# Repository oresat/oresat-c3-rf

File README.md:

# oresat-c3-rf
RF Sub systems for the C3 board.  This includes the transeiver ICs and all front-end components for the uplink and downlink radios.

## [AxSem_Profiles](AxSem_Profiles)
These are a bunch of profiles that initialize the AxSem RadioLab configuration program for testing and experiments.

## [KiCad](KiCad)
Evaluation board schematics and layouts in KiCad. Some of the older Eagle CAD boards are here converted to KiCAD.

## [block-diagrams](block-diagrams)
Block diagrams of the L band receiver and UHF transceiver hardware.

## [bom](bom)
Inventory and bill-of-materials (BOMs) for evaluation boards.

## [eagle](eagle)
Evaluation board schematics and layouts in EAGLE CAD.

## [link-models](link-models)
Complete link models for command/engineering channels, telemetry/public channels, and bulk mission data channels.

## [measurements](measurements)
Evaluation board measurements using lab tools.

## [simulations](simulations)
Evaluation board simulations using ADS and/or HFSS.

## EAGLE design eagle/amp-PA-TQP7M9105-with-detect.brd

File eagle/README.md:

## EAGLE CAD
Evaluation boards for the C3 board radios.

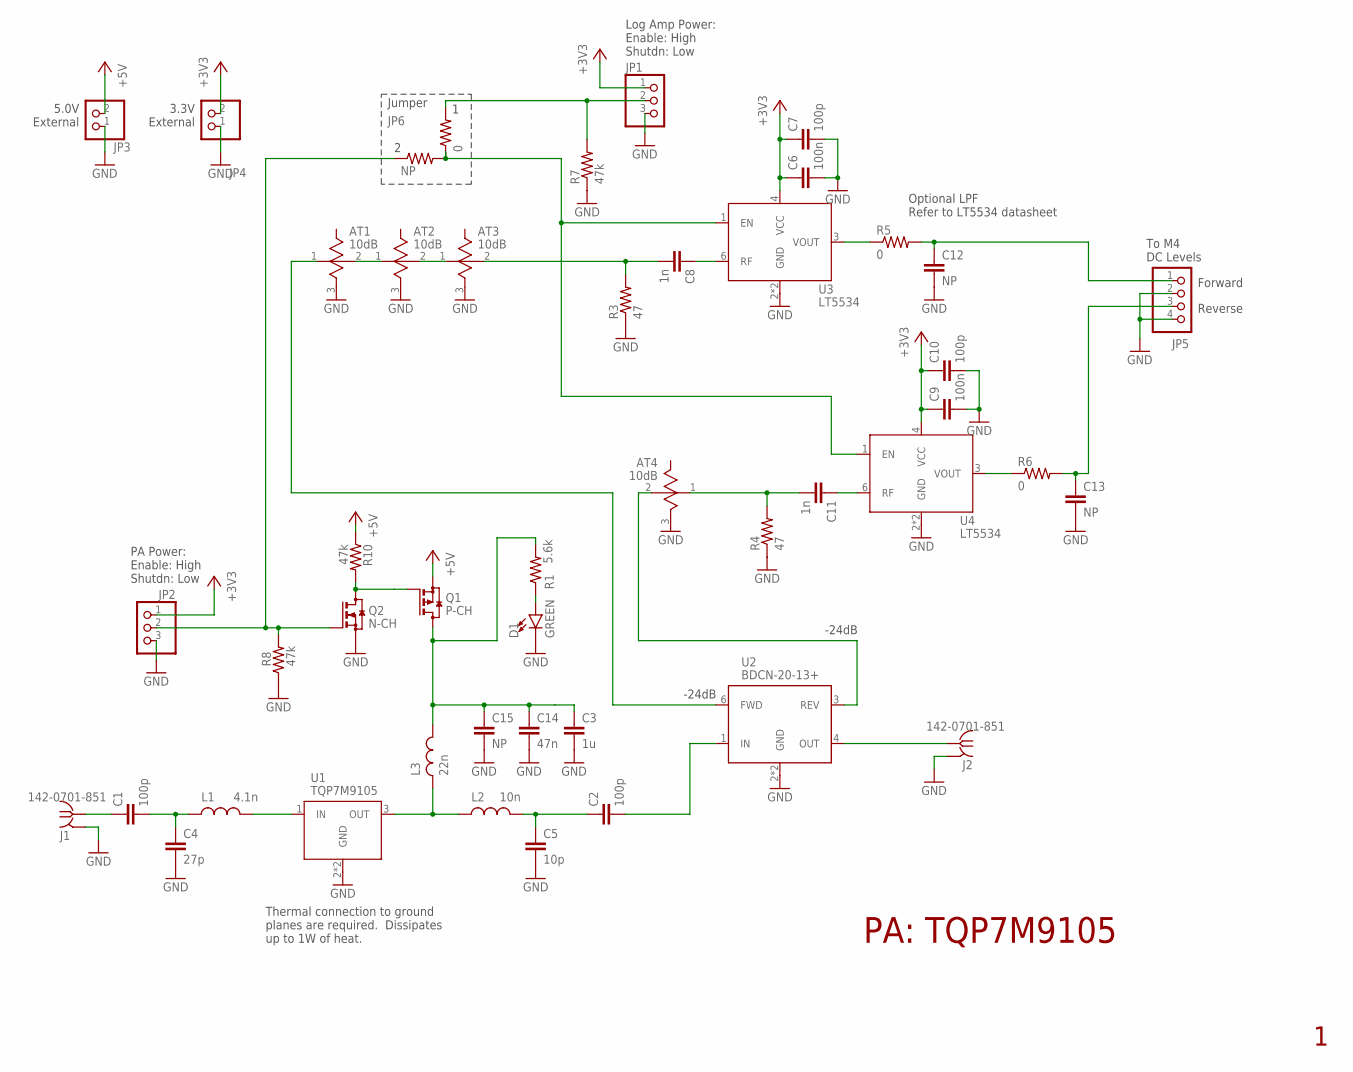
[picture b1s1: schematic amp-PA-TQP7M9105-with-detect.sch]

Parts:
AT1: 10dB; 0805
AT2, AT3, AT4: 10dB; 0603
C1: 100p; .0402-C-NOSILK
C2: 100p; .0603-C-NOSILK
C3: 1u; .0603-B-NOSILK
C4: 27p; .0402-C-NOSILK
C5: 10p; .0603-C-NOSILK
C6, C9: 100n; .0603-B-NOSILK
C7, C10: 100p; .0603-B-NOSILK
C8, C11: 1n; .0402-C-NOSILK
C12, C13, C15: NP; .0603-B-NOSILK
C14: 47n; .0603-B-NOSILK
D1: GREEN; LED-0603
J1, J2: 142-0701-851
JP1, JP2: PINHD-1X3; 1X03
JP3, JP4: PINHD-1X2; 1X02
JP5: PINHD-1X4; 1X04
JP6: NP; .0603-B-NOSILK
L1: 4.1n; .0402-C-NOSILK
L2: 10n; .0603-C-NOSILK@1
L3: 22n; .0805-C-NOSILK
Q1: P-CH; SOT23
Q2: N-CH; SOT23
R1: 5.6k; .0603-B-NOSILK
R3, R4: 47; .0402-C-NOSILK
R5, R6, R9: 0; .0603-B-NOSILK
R7, R8, R10: 47k; .0402-B-NOSILK
U1: TQP7M9105
U2: BDCN-20-13+
U3, U4: LT5534; SC70

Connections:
+3V3: C6.1, C7.1, C9.1, C10.1, JP1.1, JP2.1, JP4.2, U3.4 (VCC), U4.4 (VCC)
+5V: JP3.2, Q1.2 (S), R10.1
CAPS: C3.1, C14.1, C15.1, L3.2, Q1.3 (D), R1.2
FWD: C12.1, JP5.1, R5.2
GND: AT1.3 (GND), AT2.3 (GND), AT3.3 (GND), AT4.3 (GND), C3.2, C4.2, C5.2, C6.2, C7.2, C9.2, C10.2, C12.2, C13.2, C14.2, C15.2, D1.C, J1.GND1 (GND), J1.GND2 (GND), J1.GND3 (GND), J1.GND4 (GND), J2.GND1 (GND), J2.GND2 (GND), J2.GND3 (GND), J2.GND4 (GND), JP1.3, JP2.3, JP3.1, JP4.1, JP5.2, JP5.4, Q2.2 (S), R3.1, R4.1, R7.1, R8.1, U1.2 (GND), U1.PAD (GND), U2.2 (GND), U2.5 (GND), U3.2 (GND), U3.5 (GND), U4.2 (GND), U4.5 (GND)
unnamed: C1.1, J1.RF1 (RF)
unnamed: C2.2, U2.1 (IN)
unnamed: C1.2, C4.1, L1.1
unnamed: L1.2, U1.1 (IN)
unnamed: L2.1, L3.1, U1.3 (OUT)
unnamed: C2.1, C5.1, L2.2
unnamed: J2.RF1 (RF), U2.4 (OUT)
unnamed: C8.1, U3.6 (RF)
unnamed: AT3.2, C8.2, R3.2
unnamed: JP1.2, R7.2, R9.2
unnamed: C11.1, U4.6 (RF)
unnamed: AT4.1, C11.2, R4.2
unnamed: JP6.2, R9.1, U3.1 (EN), U4.1 (EN)
unnamed: AT1.1, U2.6 (FWD)
unnamed: AT1.2, AT2.1
unnamed: AT2.2, AT3.1
unnamed: R5.1, U3.3 (VOUT)
unnamed: R6.1, U4.3 (VOUT)
unnamed: AT4.2, U2.3 (REV)
unnamed: Q1.1 (G), Q2.3 (D), R10.2
unnamed: JP2.2, JP6.1, Q2.1 (G), R8.2
unnamed: D1.A, R1.1
REV: C13.1, JP5.3, R6.2

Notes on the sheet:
PA: TQP7M9105
Log Amp Power: Enable: High Shutdn: Low
To M4 DC Levels
Forward
Reverse
3.3V External
-24dB
PA Power: Enable: High Shutdn: Low
5.0V External
Optional LPF Refer to LT5534 datasheet
Thermal connection to ground planes are required. Dissipates up to 1W of heat.
Jumper

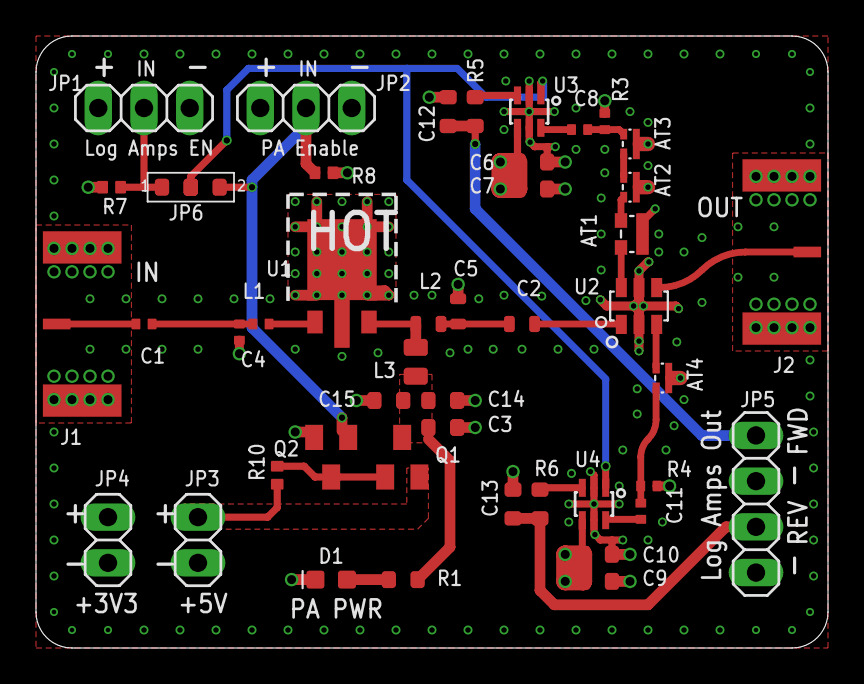
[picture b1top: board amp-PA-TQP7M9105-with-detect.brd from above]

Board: 4 copper layers, 44.0 x 34.0 mm, 46 parts (0 on the bottom side), 28 nets.

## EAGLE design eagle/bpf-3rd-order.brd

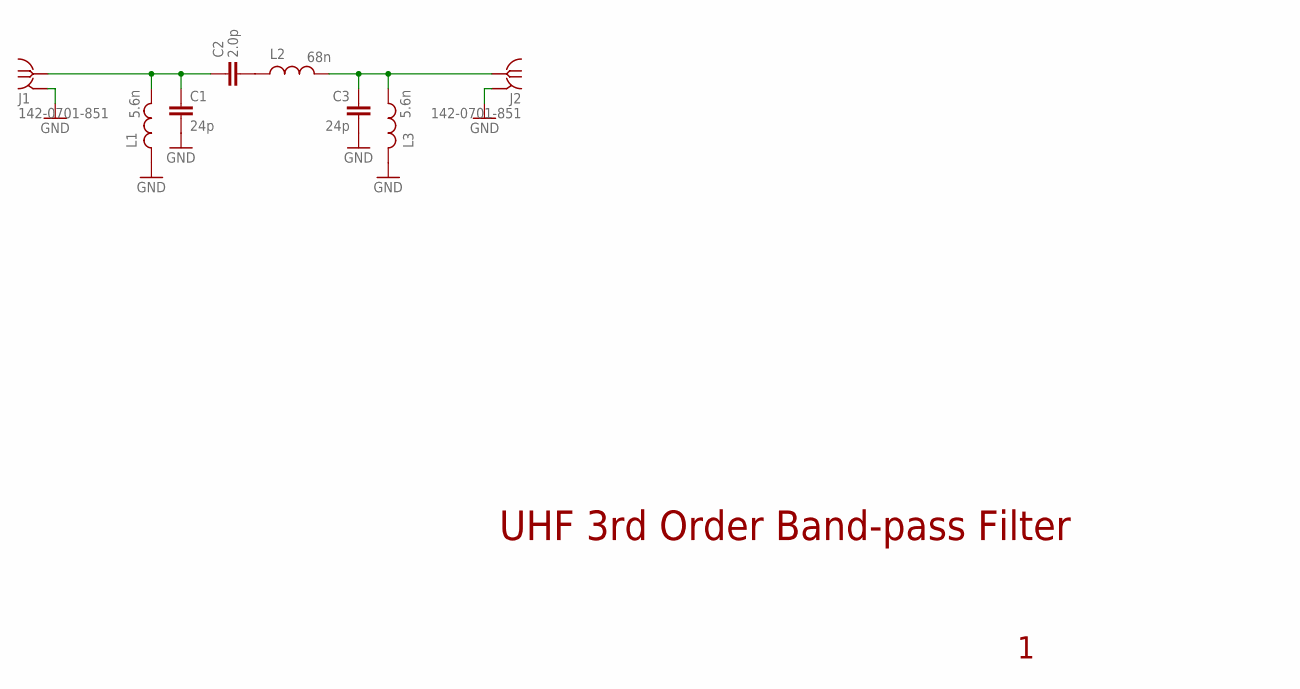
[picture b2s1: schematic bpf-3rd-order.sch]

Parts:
C1, C3: 24p; .0402-C-NOSILK
C2: 2.0p; .0402-C-NOSILK
J1, J2: 142-0701-851
L1, L3: 5.6n; .0402-C-NOSILK
L2: 68n; .0402-C-NOSILK

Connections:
GND: C1.2, C3.2, J1.GND1 (GND), J1.GND2 (GND), J1.GND3 (GND), J1.GND4 (GND), J2.GND1 (GND), J2.GND2 (GND), J2.GND3 (GND), J2.GND4 (GND), L1.1, L3.1
unnamed: C2.2, L2.1
unnamed: C1.1, C2.1, J1.RF1 (RF), L1.2
unnamed: C3.1, J2.RF1 (RF), L2.2, L3.2

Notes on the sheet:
UHF 3rd Order Band-pass Filter

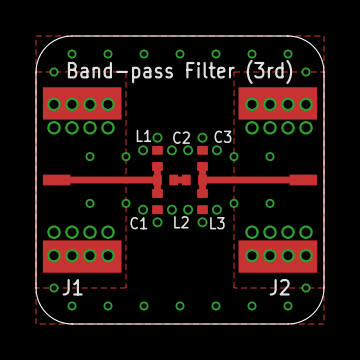
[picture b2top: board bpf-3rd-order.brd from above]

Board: 4 copper layers, 16.0 x 16.0 mm, 8 parts (0 on the bottom side), 4 nets.

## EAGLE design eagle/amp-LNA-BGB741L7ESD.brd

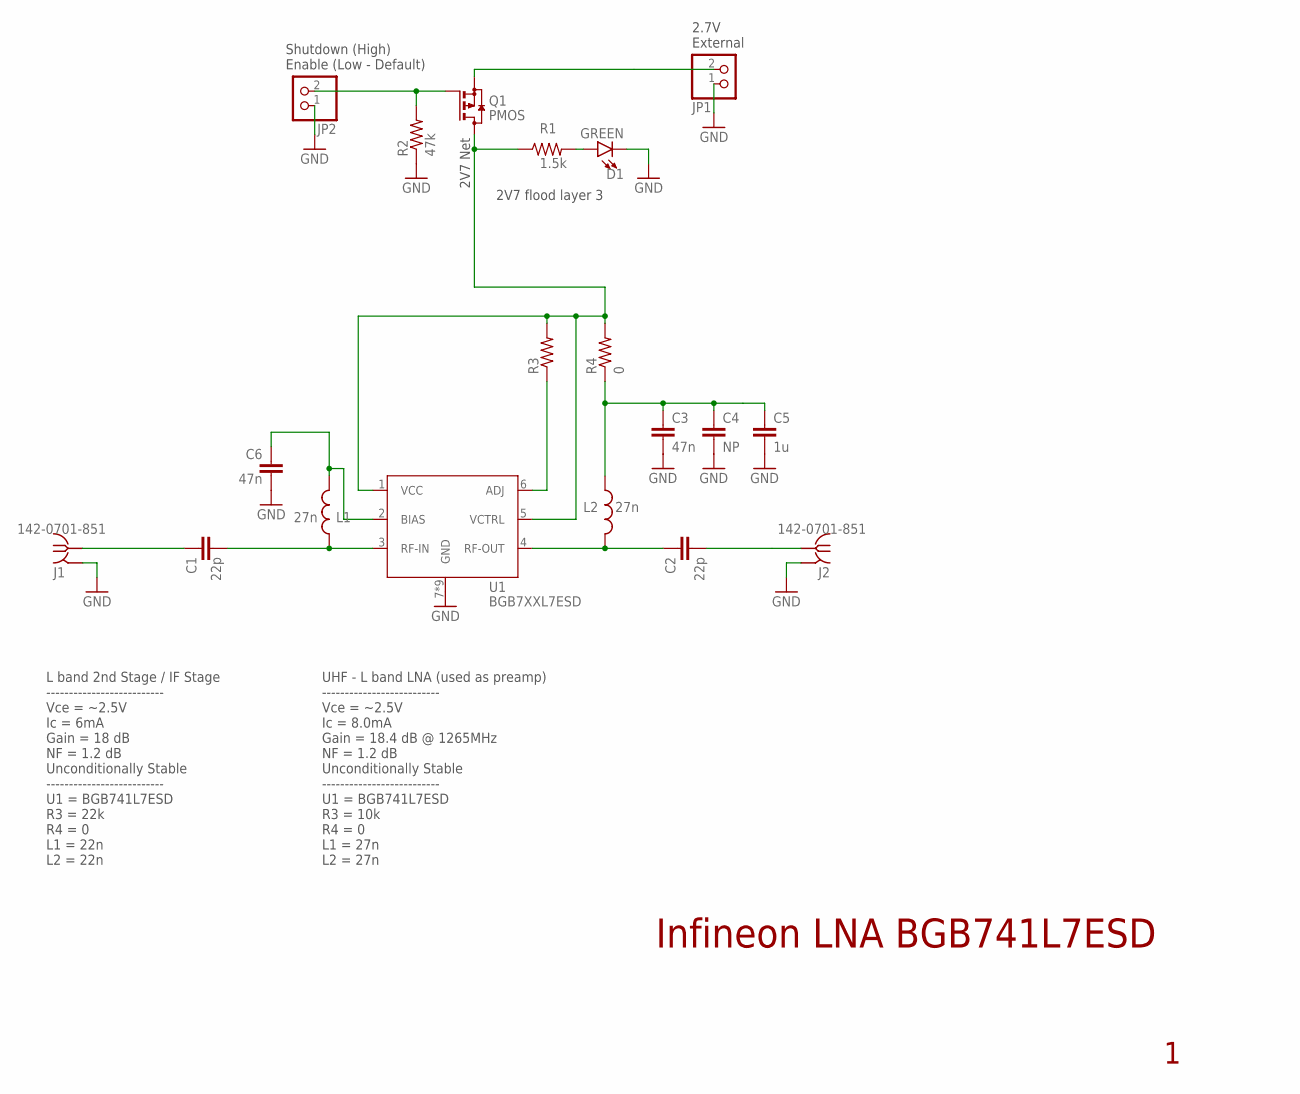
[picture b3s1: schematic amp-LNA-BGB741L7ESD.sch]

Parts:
C1, C2: 22p; .0402-C-NOSILK
C3, C6: 47n; .0603-B-NOSILK
C4: NP; .0603-B-NOSILK
C5: 1u; .0603-B-NOSILK
D1: GREEN; LED-0603
J1, J2: 142-0701-851
JP1, JP2: PINHD-1X2; 1X02
L1, L2: 27n; .0603-C-NOSILK
Q1: PMOS; SOT23
R1: 1.5k; .0603-B-NOSILK
R2: 47k; .0402-B-NOSILK
R3: 27k / NP; .0603-B-NOSILK
R4: 0; .0603-B-NOSILK
U1: BGB7XXL7ESD

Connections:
2V7: Q1.3 (D), R1.1, R3.2, R4.2, U1.1 (VCC), U1.5 (VCTRL)
GND: C3.2, C4.2, C5.2, C6.2, D1.C, J1.GND1 (GND), J1.GND2 (GND), J1.GND3 (GND), J1.GND4 (GND), J2.GND1 (GND), J2.GND2 (GND), J2.GND3 (GND), J2.GND4 (GND), JP1.1, JP2.1, R2.1, U1.7 (GND), U1.8 (GND), U1.9 (GND), U1.10 (GND), U1.11 (GND), U1.12 (GND), U1.13 (GND), U1.14 (GND), U1.15 (GND)
unnamed: JP2.2, Q1.1 (G), R2.2
unnamed: C3.1, C4.1, C5.1, L2.1, R4.1
unnamed: C2.1, L2.2, U1.4 (RF-OUT)
unnamed: R3.1, U1.6 (ADJ)
unnamed: C6.1, L1.2, U1.2 (BIAS)
unnamed: D1.A, R1.2
unnamed: C1.2, L1.1, U1.3 (RF-IN)
RF-IN: C1.1, J1.RF1 (RF)
RF_OUT: C2.2, J2.RF1 (RF)
VEXT: JP1.2, Q1.2 (S)

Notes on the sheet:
Infineon LNA BGB741L7ESD
2.7V External
Shutdown (High) Enable (Low - Default)
2V7 flood layer 3
2V7 Net
L band 2nd Stage / IF Stage -------------------------- Vce = ~2.5V Ic = 6mA Gain = 18 dB NF = 1.2 dB Unconditionally Stable -------------------------- U1 = BGB741L7ESD R3 = 22k R4 = 0 L1 = 22n L2 = 22n
UHF - L band LNA (used as preamp) -------------------------- Vce = ~2.5V Ic = 8.0mA Gain = 18.4 dB @ 1265MHz NF = 1.2 dB Unconditionally Stable -------------------------- U1 = BGB741L7ESD R3 = 10k R4 = 0 L1 = 27n L2 = 27n

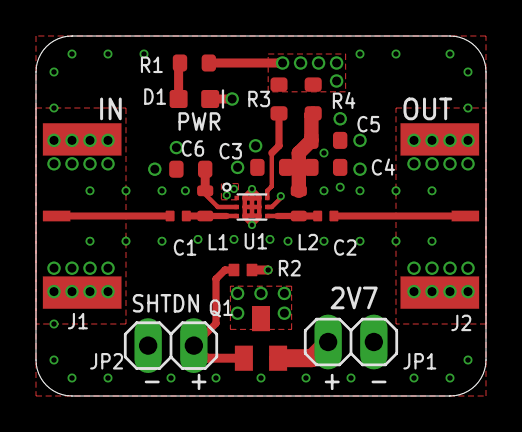
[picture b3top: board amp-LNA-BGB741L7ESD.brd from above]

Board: 4 copper layers, 25.0 x 20.0 mm, 19 parts (0 on the bottom side), 12 nets.

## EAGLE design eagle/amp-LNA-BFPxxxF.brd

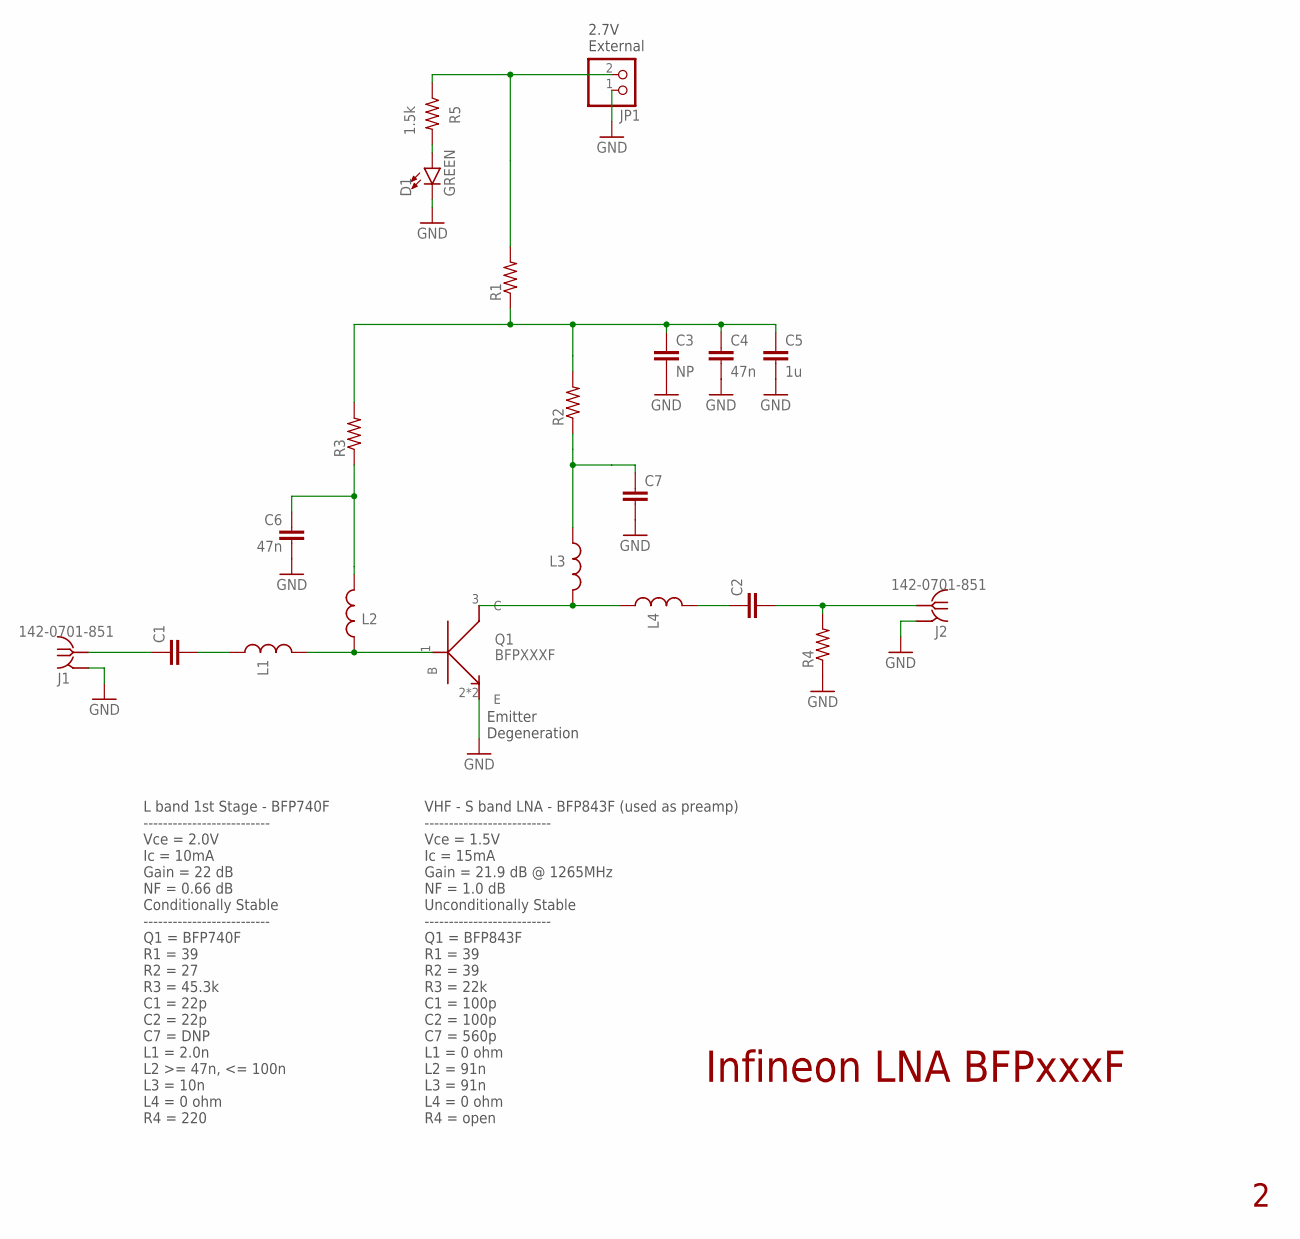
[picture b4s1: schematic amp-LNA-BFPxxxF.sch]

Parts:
C1, C2: C-EU0402-C-NOSILK; .0402-C-NOSILK
C3: NP; .0603-C-NOSILK
C4, C6: 47n; .0603-C-NOSILK
C5: 1u; .0603-C-NOSILK
C7: C-EU0402-B-NOSILK; .0402-B-NOSILK
D1: GREEN; LED-0603
J1, J2: 142-0701-851
JP1: PINHD-1X2; 1X02
L1, L4: L-US0402-C-NOSILK; .0402-C-NOSILK
L2, L3: L-US0603-C-NOSILK; .0603-C-NOSILK
Q1: BFPXXXF; TSFP4
R1, R2, R3, R4: R-US_0603-C-NOSILK; .0603-C-NOSILK
R5: 1.5k; .0603-C-NOSILK

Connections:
2V7: JP1.2, R1.2, R5.1
B: L1.2, L2.1, Q1.1 (B)
C: L3.2, L4.1, Q1.3 (C)
CAPS: C3.1, C4.1, C5.1, R1.1, R2.2, R3.2
GND: C3.2, C4.2, C5.2, C6.2, C7.2, D1.C, J1.GND1 (GND), J1.GND2 (GND), J1.GND3 (GND), J1.GND4 (GND), J2.GND1 (GND), J2.GND2 (GND), J2.GND3 (GND), J2.GND4 (GND), JP1.1, Q1.2 (E), Q1.4 (E), R4.1
unnamed: C2.1, L4.2
unnamed: C1.2, L1.1
unnamed: C7.1, L3.1, R2.1
unnamed: C6.1, L2.2, R3.1
unnamed: D1.A, R5.2
RF_IN: C1.1, J1.RF1 (RF)
RF_OUT: C2.2, J2.RF1 (RF), R4.2

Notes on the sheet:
Infineon LNA BFPxxxF
2.7V External
L band 1st Stage - BFP740F -------------------------- Vce = 2.0V Ic = 10mA Gain = 22 dB NF = 0.66 dB Conditionally Stable -------------------------- Q1 = BFP740F R1 = 39 R2 = 27 R3 = 45.3k C1 = 22p C2 = 22p C7 = DNP L1 = 2.0n L2 >= 47n, <= 100n L3 = 10n L4 = 0 ohm R4 = 220
Emitter Degeneration
VHF - S band LNA - BFP843F (used as preamp) -------------------------- Vce = 1.5V Ic = 15mA Gain = 21.9 dB @ 1265MHz NF = 1.0 dB Unconditionally Stable -------------------------- Q1 = BFP843F R1 = 39 R2 = 39 R3 = 22k C1 = 100p C2 = 100p C7 = 560p L1 = 0 ohm L2 = 91n L3 = 91n L4 = 0 ohm R4 = open

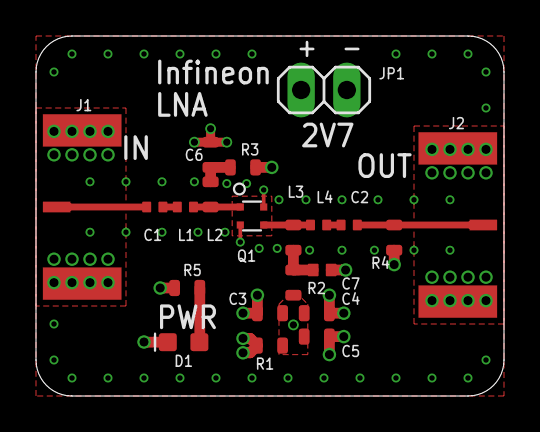
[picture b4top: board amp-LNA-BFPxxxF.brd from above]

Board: 4 copper layers, 26.0 x 20.0 mm, 21 parts (0 on the bottom side), 12 nets.

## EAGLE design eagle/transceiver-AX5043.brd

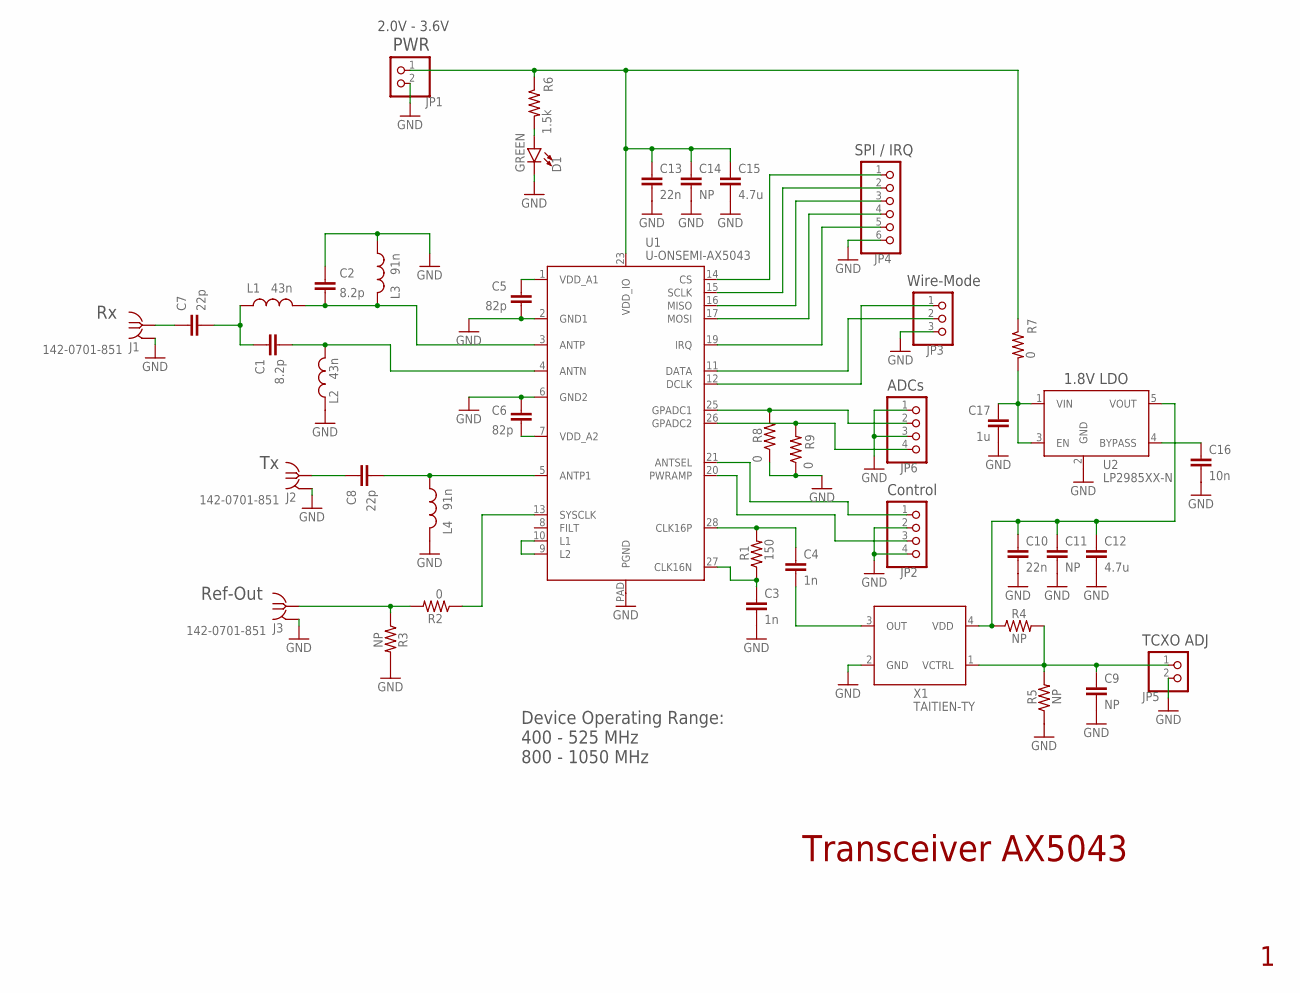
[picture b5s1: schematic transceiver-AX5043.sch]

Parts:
C1, C2: 8.2p; .0402-C-NOSILK
C3, C4: 1n; .0402-C-NOSILK
C5, C6: 82p; .0402-C-NOSILK
C7, C8: 22p; .0402-C-NOSILK
C9, C11, C14: NP; .0603-C-NOSILK
C10, C13: 22n; .0603-C-NOSILK
C12, C15: 4.7u; .0603-C-NOSILK
C16: 10n; .0603-C-NOSILK
C17: 1u; .0603-C-NOSILK
D1: GREEN; LED-0603
J1, J2, J3: 142-0701-851
JP1, JP5: PINHD-1X2; 1X02
JP2, JP6: PINHD-1X4; 1X04
JP3: PINHD-1X3; 1X03
JP4: PINHD-1X6; 1X06
L1, L2: 43n; .0402-C-NOSILK
L3, L4: 91n; .0603-C-NOSILK
R1: 150; .0402-C-NOSILK
R2, R8, R9: 0; .0402-C-NOSILK
R3: NP; .0402-C-NOSILK
R4, R5: NP; .0603-B-NOSILK
R6: 1.5k; .0603-B-NOSILK
R7: 0; .0603-C-NOSILK
U1: U-ONSEMI-AX5043; QFN28-5X5-WITH-CENTER-PAD
U2: LP2985XX-N; SOT-23
X1: TAITIEN-TY; 2.5X2.0

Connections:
1V8: C10.1, C11.1, C12.1, R4.1, U2.5 (VOUT), X1.4 (VDD)
2V7: C13.1, C14.1, C15.1, JP1.1, R6.1, R7.1, U1.23 (VDD_IO)
ADC1: JP6.2, R8.2, U1.25 (GPADC1)
ADC2: JP6.4, R9.2, U1.26 (GPADC2)
ANTN: C1.2, L2.2, U1.4 (ANTN)
ANTP: C2.2, L1.2, L3.1, U1.3 (ANTP)
ANTP1: C8.2, L4.2, U1.5 (ANTP1)
ANTSEL: JP2.1, U1.21 (ANTSEL)
CLKN: C3.1, R1.1, U1.27 (CLK16N)
CLKP: C4.1, R1.2, U1.28 (CLK16P)
CS: JP4.1, U1.14 (CS)
DATA: JP3.2, U1.11 (DATA)
DCLK: JP3.1, U1.12 (DCLK)
GND: C2.1, C3.2, C5.2, C6.1, C9.2, C10.2, C11.2, C12.2, C13.2, C14.2, C15.2, C16.2, C17.2, D1.C, J1.GND1 (GND), J1.GND2 (GND), J1.GND3 (GND), J1.GND4 (GND), J2.GND1 (GND), J2.GND2 (GND), J2.GND3 (GND), J2.GND4 (GND), J3.GND1 (GND), J3.GND2 (GND), J3.GND3 (GND), J3.GND4 (GND), JP1.2, JP2.2, JP2.4, JP3.3, JP4.6, JP5.2, JP6.1, JP6.3, L2.1, L3.2, L4.1, R3.2, R5.1, R8.1, R9.1, U1.2 (GND1), U1.6 (GND2), U1.PAD (PGND), U2.2 (GND), X1.2 (GND)
IRQ: JP4.5, U1.19 (IRQ)
MISO: JP4.3, U1.16 (MISO)
MOSI: JP4.4, U1.17 (MOSI)
unnamed: C5.1, U1.1 (VDD_A1)
unnamed: C17.1, R7.2, U2.1 (VIN), U2.3 (EN)
unnamed: U1.9 (L2), U1.10 (L1)
unnamed: C4.2, X1.3 (OUT)
unnamed: C1.1, C7.2, L1.1
unnamed: C9.1, JP5.1, R4.2, R5.2, X1.1 (VCTRL)
unnamed: D1.A, R6.2
unnamed: C16.1, U2.4 (BYPASS)
unnamed: C6.2, U1.7 (VDD_A2)
PWRAMP: JP2.3, U1.20 (PWRAMP)
REF-OUT: J3.RF1 (RF), R2.2, R3.1
RX: C7.1, J1.RF1 (RF)
SCLK: JP4.2, U1.15 (SCLK)
SYSCLK: R2.1, U1.13 (SYSCLK)
TX: C8.1, J2.RF1 (RF)

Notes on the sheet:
Transceiver AX5043
Ref-Out
PWR
SPI / IRQ
Wire-Mode
Control
TCXO ADJ
1.8V LDO
ADCs
Device Operating Range: 400 - 525 MHz 800 - 1050 MHz
2.0V - 3.6V

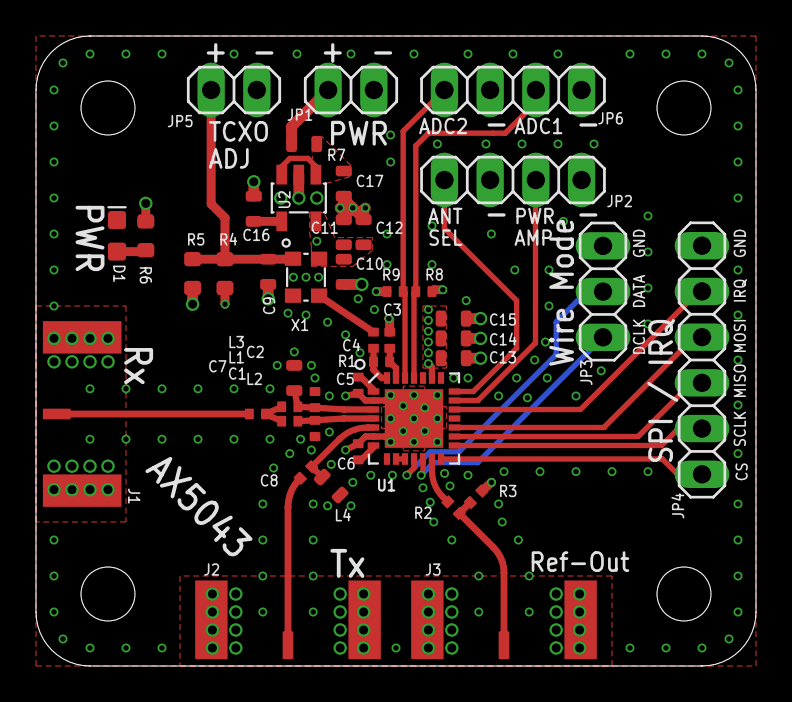
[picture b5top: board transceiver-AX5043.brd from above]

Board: 4 copper layers, 40.0 x 35.0 mm, 43 parts (0 on the bottom side), 32 nets.

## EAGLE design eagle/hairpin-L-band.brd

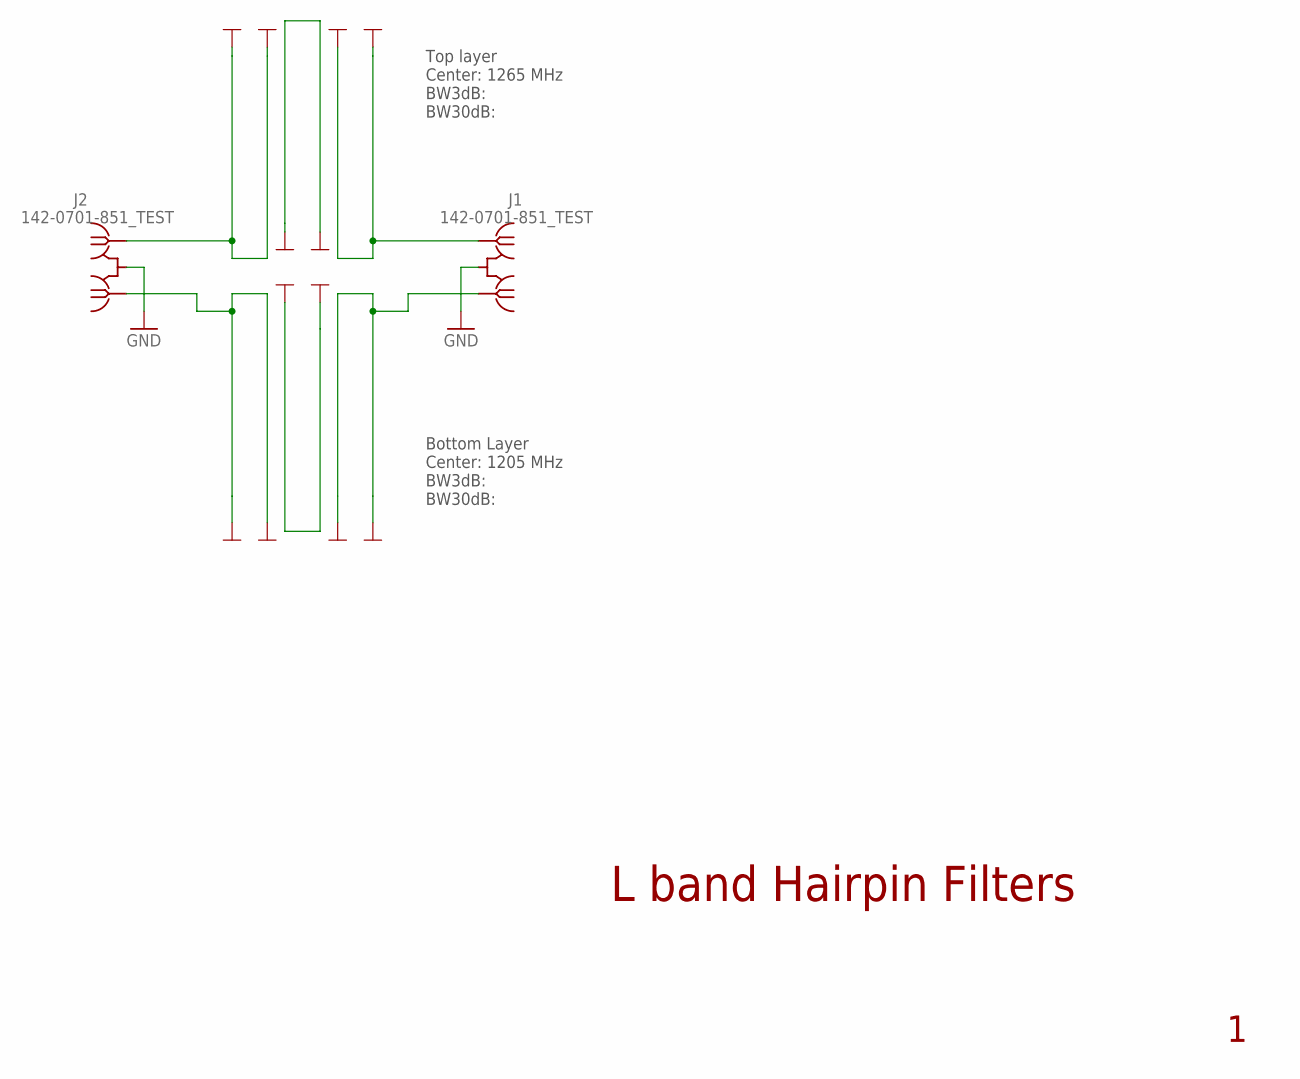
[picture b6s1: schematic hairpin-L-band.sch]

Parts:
J1, J2: 142-0701-851_TEST
U$1, U$2, U$3, U$4, U$5, U$6: PAD_0.6; 0.6MM
U$7, U$8, U$9, U$10, U$11, U$12: PAD_0.6_B; 0.6MM_B

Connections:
BLEFT: J2.RF2, U$11.END, U$12.END
BMID: U$9.END, U$10.END
BRIGHT: J1.RF2, U$7.END, U$8.END
GND: J1.GND1 (GND), J1.GND2 (GND), J1.GND3 (GND), J1.GND4 (GND), J2.GND1 (GND), J2.GND2 (GND), J2.GND3 (GND), J2.GND4 (GND)
TLEFT: J2.RF1, U$5.END, U$6.END
TMID: U$3.END, U$4.END
TRIGHT: J1.RF1, U$1.END, U$2.END

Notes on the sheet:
L band Hairpin Filters
Top layer Center: 1265 MHz BW3dB: BW30dB:
Bottom Layer Center: 1205 MHz BW3dB: BW30dB:

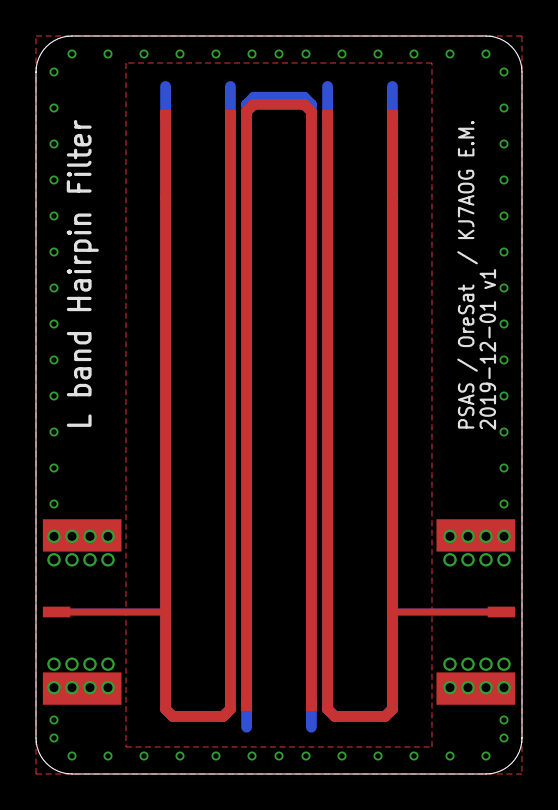
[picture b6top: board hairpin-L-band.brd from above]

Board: 4 copper layers, 27.0 x 41.0 mm, 14 parts (0 on the bottom side), 7 nets.

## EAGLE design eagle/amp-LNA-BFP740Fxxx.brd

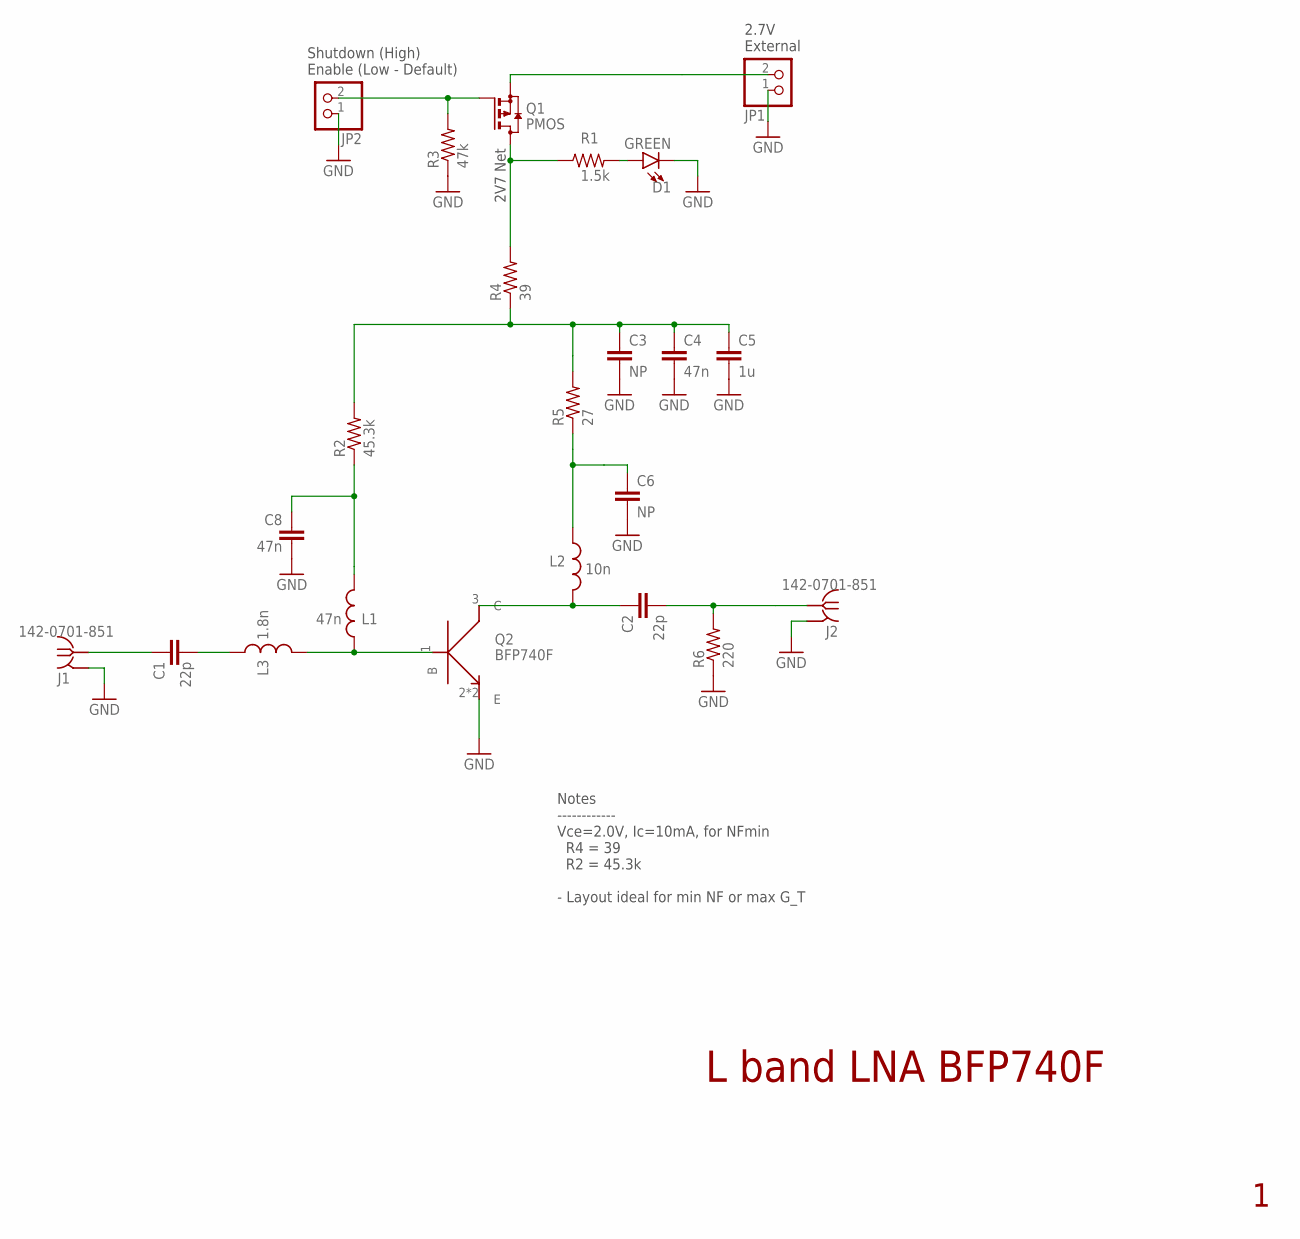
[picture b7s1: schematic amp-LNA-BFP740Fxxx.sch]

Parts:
C1, C2: 22p; .0402-C-NOSILK
C3: NP; .0603-C-NOSILK
C4, C8: 47n; .0603-C-NOSILK
C5: 1u; .0603-C-NOSILK
C6: NP; .0402-B-NOSILK
D1: GREEN; LED-0603
J1, J2: 142-0701-851
JP1, JP2: PINHD-1X2; 1X02
L1: 47n; .0603-C-NOSILK
L2: 10n; .0603-C-NOSILK
L3: 1.8n; .0402-C-NOSILK
Q1: PMOS; SOT23
Q2: BFP740F; TSFP4
R1: 1.5k; .0603-C-NOSILK
R2: 45.3k; .0603-C-NOSILK
R3: 47k; .0402-B-NOSILK
R4: 39; .0603-C-NOSILK
R5: 27; .0603-C-NOSILK
R6: 220; .0603-C-NOSILK

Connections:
2V7: Q1.3 (D), R1.1, R4.2
B: L1.1, L3.2, Q2.1 (B)
C: C2.1, L2.2, Q2.3 (C)
CAPS: C3.1, C4.1, C5.1, R2.2, R4.1, R5.2
GND: C3.2, C4.2, C5.2, C6.2, C8.2, D1.C, J1.GND1 (GND), J1.GND2 (GND), J1.GND3 (GND), J1.GND4 (GND), J2.GND1 (GND), J2.GND2 (GND), J2.GND3 (GND), J2.GND4 (GND), JP1.1, JP2.1, Q2.2 (E), Q2.4 (E), R3.1, R6.1
unnamed: JP2.2, Q1.1 (G), R3.2
unnamed: C1.2, L3.1
unnamed: C6.1, L2.1, R5.1
unnamed: C8.1, L1.2, R2.1
unnamed: D1.A, R1.2
RF_IN: C1.1, J1.RF1 (RF)
RF_OUT: C2.2, J2.RF1 (RF), R6.2
VEXT: JP1.2, Q1.2 (S)

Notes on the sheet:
L band LNA BFP740F
2.7V External
Shutdown (High) Enable (Low - Default)
2V7 Net
Notes ------------ Vce=2.0V, Ic=10mA, for NFmin R4 = 39 R2 = 45.3k - Layout ideal for min NF or max G_T

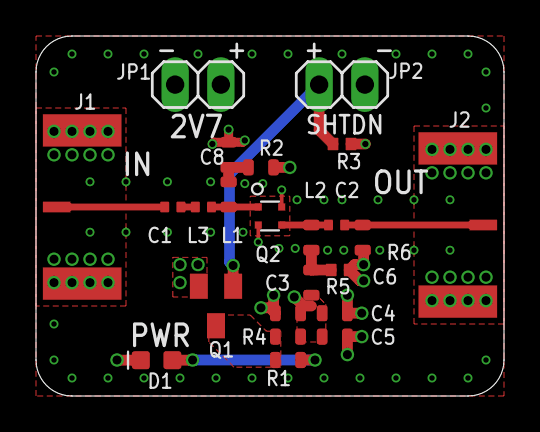
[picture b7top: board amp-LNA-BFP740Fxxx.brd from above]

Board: 4 copper layers, 26.0 x 20.0 mm, 23 parts (0 on the bottom side), 13 nets.

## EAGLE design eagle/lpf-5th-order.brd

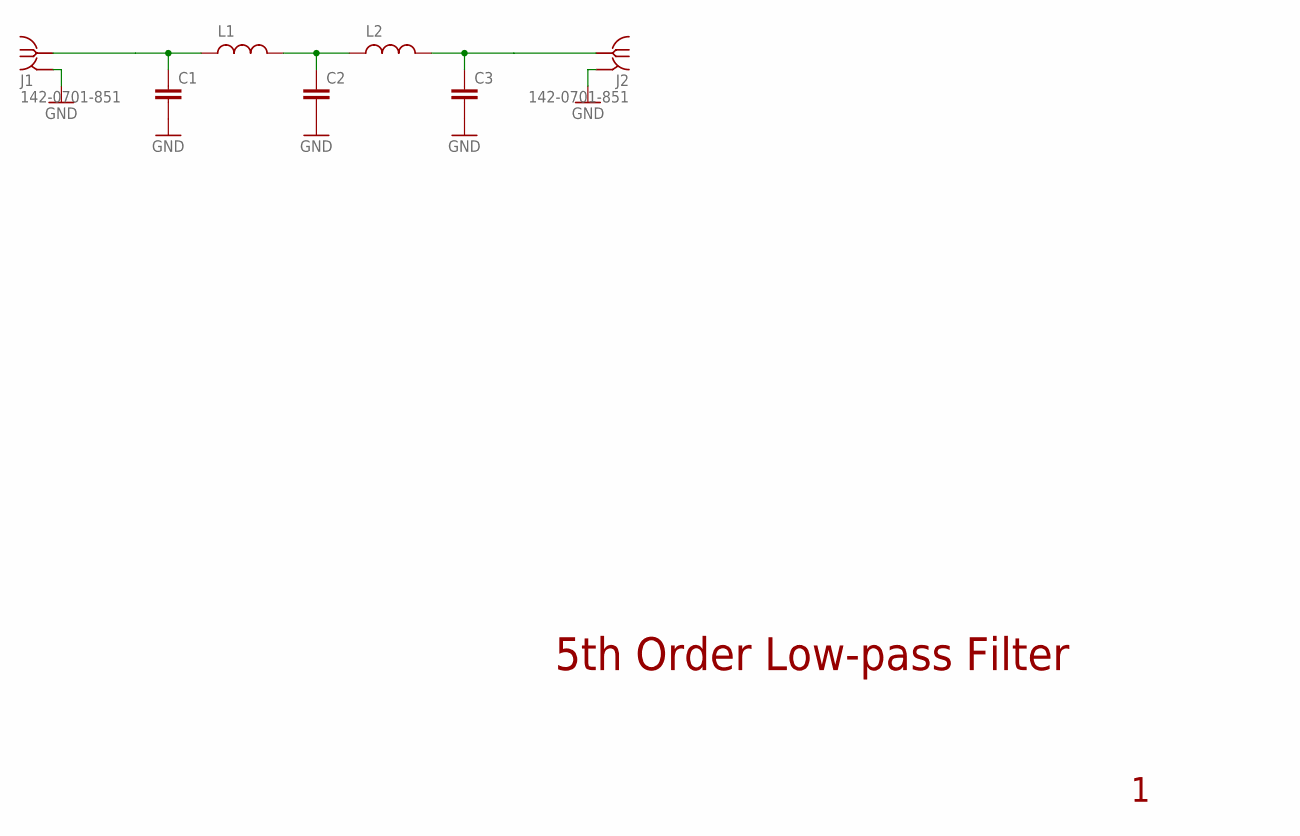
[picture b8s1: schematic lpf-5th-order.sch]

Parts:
C1, C2, C3: C-EU0402-C-NOSILK; .0402-C-NOSILK
J1, J2: 142-0701-851
L1, L2: L-US0402-C-NOSILK; .0402-C-NOSILK

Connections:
GND: C1.2, C2.2, C3.2, J1.GND1 (GND), J1.GND2 (GND), J1.GND3 (GND), J1.GND4 (GND), J2.GND1 (GND), J2.GND2 (GND), J2.GND3 (GND), J2.GND4 (GND)
unnamed: C2.1, L1.2, L2.1
RF-IN: C1.1, J1.RF1 (RF), L1.1
RF-OUT: C3.1, J2.RF1 (RF), L2.2

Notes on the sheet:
5th Order Low-pass Filter

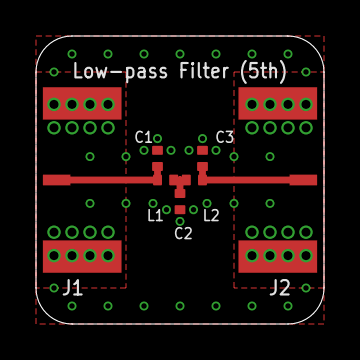
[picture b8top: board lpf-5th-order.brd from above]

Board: 4 copper layers, 16.0 x 16.0 mm, 7 parts (0 on the bottom side), 4 nets.

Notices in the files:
parts and their libraries:
SparkFun-LED: Licensing: Creative Commons ShareAlike 4.0 International - https://creativecommons.org/licenses/by-sa/4.0
